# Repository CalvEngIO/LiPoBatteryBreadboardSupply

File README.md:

# LiPoBatteryBreadboardSupply
Breadboard power supply adapter for a Lithium Polymer Battery

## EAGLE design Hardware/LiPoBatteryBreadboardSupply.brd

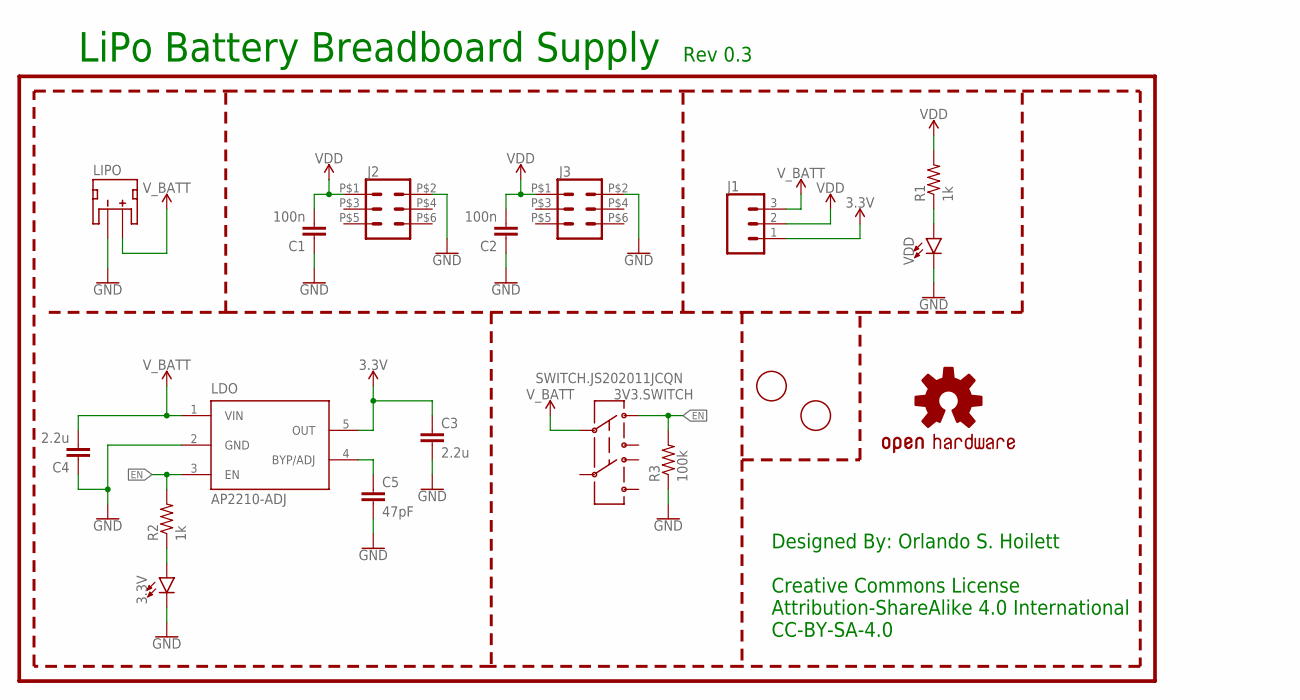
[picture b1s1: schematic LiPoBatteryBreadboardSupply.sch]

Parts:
3.3V: LED0603; LED-0603
3V3.SWITCH: SWITCH.JS202011JCQN; SWITCH.00
C1, C2: 100n; C0603
C3, C4: 2.2u; C0603
C5: 47pF; C0402
FD1, FD2: FIDUCIAL; FIDUCIAL_1MM
J1: CONN_03; 1X03
J2, J3: JMP.03X2HEADERS; JMP.03X2
LDO: AP2210-ADJ; SOT23-5
LIPO: JST_2MM_MALE; JST-2-SMD
LOGO1: OSHW-LOGOS; OSHW-LOGO-S
R1, R2: 1k; R0402
R3: 100k; R0402
U$1: HANDLE.1HANDLE.025; HANDLE.025
U$6: HANDLE.1HANDLE.08; HANDLE.08
VDD: LED0603; LED-0603

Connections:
3.3V: C3.1, J1.1, LDO.5 (OUT)
EN: 3V3.SWITCH.1, LDO.3 (EN), R2.2, R3.2
GND: 3.3V.C, C1.1, C2.1, C3.2, C4.1, C5.2, J2.P$2 (2), J3.P$2 (2), LDO.2 (GND), LIPO.1 (-), R3.1, VDD.C
unnamed: 3.3V.A, R2.1
unnamed: R1.1, VDD.A
unnamed: C5.1, LDO.4 (BYP/ADJ)
VDD: C1.2, C2.2, J1.2, J2.P$1 (1), J3.P$1 (1), R1.2
V_BATT: 3V3.SWITCH.2, C4.2, J1.3, LDO.1 (VIN), LIPO.2 (+)

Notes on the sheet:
Creative Commons License Attribution-ShareAlike 4.0 International CC-BY-SA-4.0
Designed By: Orlando S. Hoilett
LiPo Battery Breadboard Supply
Rev 0.3

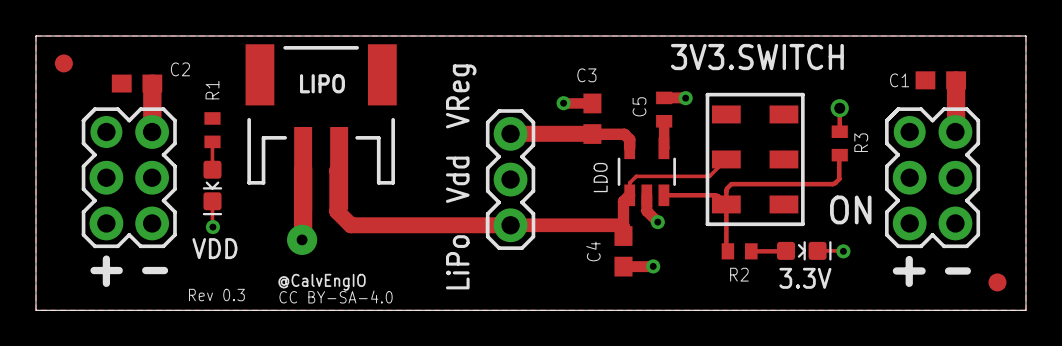
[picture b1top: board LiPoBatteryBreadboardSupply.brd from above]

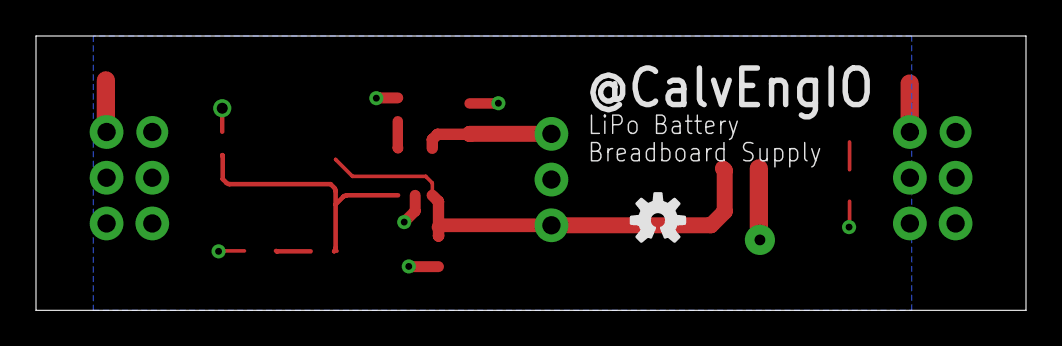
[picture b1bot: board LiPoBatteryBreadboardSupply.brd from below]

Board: 2 copper layers, 55.0 x 15.2 mm, 21 parts (2 on the bottom side), 8 nets.

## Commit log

2017-03-02 inital commit, very incomplete and untested
2017-03-02 more edits, need tons of editing
2017-03-05 Create LICENSE-Hardware
2017-05-08 changes to the silkscreen and changes to the BOM
2017-05-08 changes to BOM and change in value of Cbypass on regulator in schematic
2017-07-28 more updates

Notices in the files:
parts and their libraries:
SparkFun-Connectors: Licensing: Creative Commons ShareAlike 4.0 International - https://creativecommons.org/licenses/by-sa/4.0
